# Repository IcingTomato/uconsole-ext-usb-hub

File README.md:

Licence | OSHWA
:-------------------------:|:-------------------------:
 | 

# uConsole USB Hub

This extension board adds 4 additional USB ports to the [uConsole](https://www.clockworkpi.com/uconsole).

## Schematic

## PCB

## Changelog
* 0.1.1
    * Schematic
        * No changes
    * PCB
        * Add OSHW certification
        * Add some info labels and QR code to this repo
* 0.1.0 -- **Production Release**
    * Schematic
        * `HUB_RESET` is now connected to `GPIO28`
        * `U3`, `U4`, `U5`, `U6` are rotated to simplify pcb
    * PCB
        * First PCB version
* 0.0.2
    * Schematic
        * Add speakers
* 0.0.1
    * Initial release

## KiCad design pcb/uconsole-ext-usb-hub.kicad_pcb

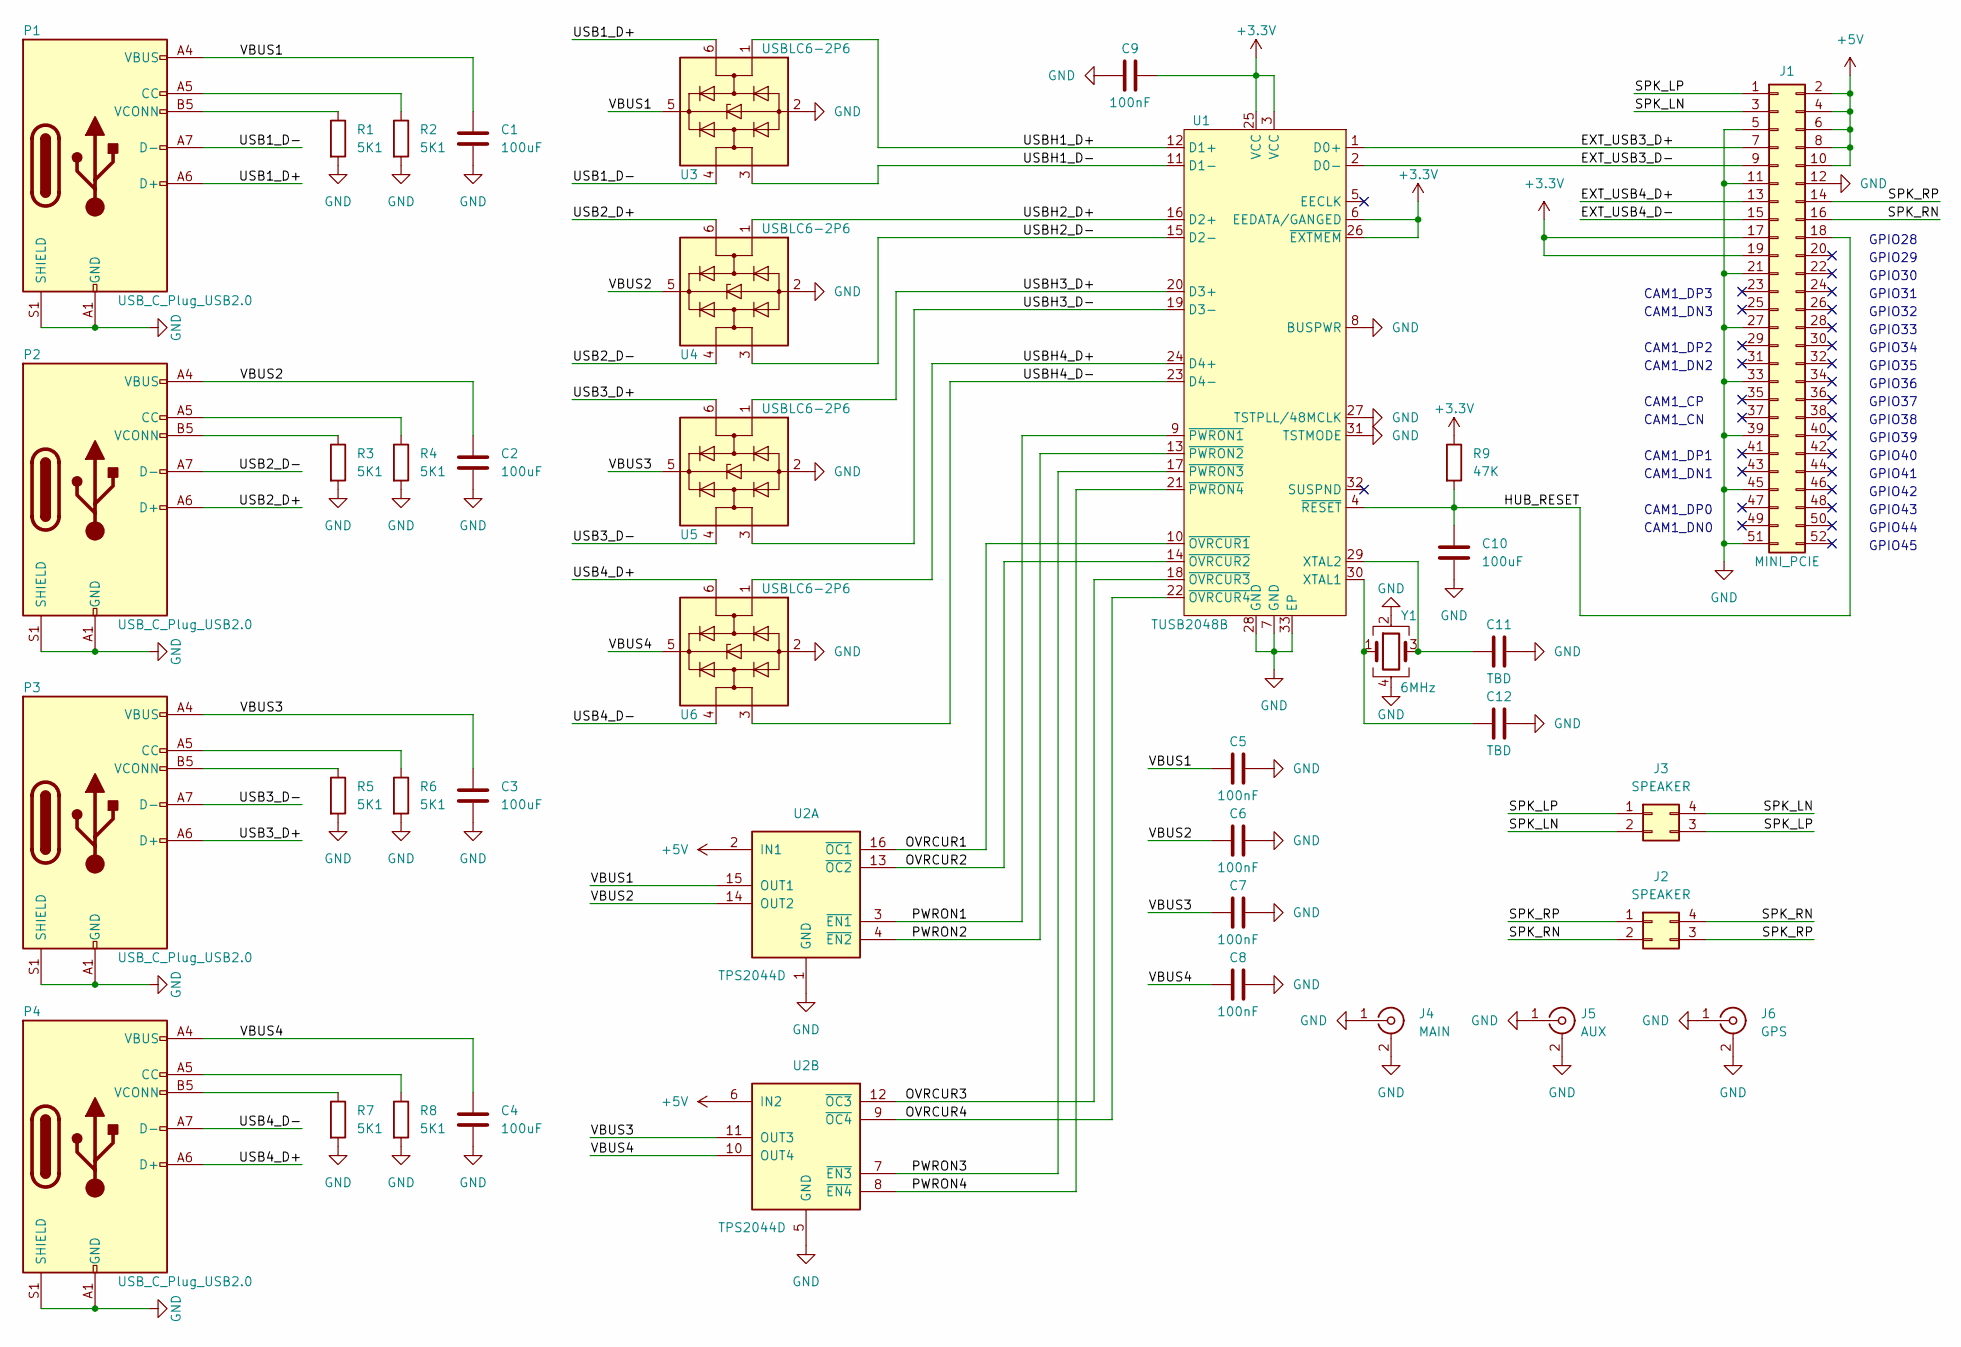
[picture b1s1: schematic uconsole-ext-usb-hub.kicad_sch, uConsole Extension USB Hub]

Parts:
C1, C2, C3, C4, C10: 100uF; C_0805_2012Metric
C5, C6, C7, C8, C9: 100nF; C_0603_1608Metric
C11, C12: TBD; C_0603_1608Metric
J1: MINI_PCIE; mini_pcie_edge
J2, J3: SPEAKER; uConsole_speaker
J4: MAIN; U.FL_Hirose_U.FL-R-SMT-1_Vertical
J5: AUX; U.FL_Hirose_U.FL-R-SMT-1_Vertical
J6: GPS; U.FL_Hirose_U.FL-R-SMT-1_Vertical
P1, P2, P3, P4: USB_C_Plug_USB2.0; USB_C_Receptacle_GCT_USB4105-xx-A_16P_TopMnt_Horizontal
R1, R2, R3, R4, R5, R6, R7, R8: 5K1; R_0603_1608Metric
R9: 47K; R_0603_1608Metric
U1: TUSB2048B; QFN-32-1EP_5x5mm_P0.5mm_EP3.3x3.3mm_ThermalVias
U2: TPS2044D; SOIC-16_3.9x9.9mm_P1.27mm
U3, U4, U5, U6: USBLC6-2P6; SOT-666
Y1: 6MHz; Crystal_SMD_2016-4Pin_2.0x1.6mm

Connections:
+3.3V: C9.1, J1.17, J1.19, R9.1, U1.3 (VCC), U1.6 (EEDATA/GANGED), U1.25 (VCC), U1.26 (~EXTMEM)
+5V: J1.2, J1.4, J1.6, J1.8, J1.10, U2.2 (IN1), U2.6 (IN2)
/EXT_USB3_D+: J1.7, U1.1 (D0+)
/EXT_USB3_D-: J1.9, U1.2 (D0-)
/EXT_USB4_D+: J1.13
/EXT_USB4_D-: J1.15
/HUB_RESET: C10.1, J1.18, R9.2, U1.4 (~RESET)
/OVRCUR1: U1.10 (~OVRCUR1), U2.16 (~OC1)
/OVRCUR2: U1.14 (~OVRCUR2), U2.13 (~OC2)
/OVRCUR3: U1.18 (~OVRCUR3), U2.12 (~OC3)
/OVRCUR4: U1.22 (~OVRCUR4), U2.9 (~OC4)
/PWRON1: U1.9 (~PWRON1), U2.3 (~EN1)
/PWRON2: U1.13 (~PWRON2), U2.4 (~EN2)
/PWRON3: U1.17 (~PWRON3), U2.7 (~EN3)
/PWRON4: U1.21 (~PWRON4), U2.8 (~EN4)
/SPK_LN: J1.3, J3.2, J3.4
/SPK_LP: J1.1, J3.1, J3.3
/SPK_RN: J1.16, J2.2, J2.4
/SPK_RP: J1.14, J2.1, J2.3
/USB1_D+: P1.A6 (D+), U3.6 (I/O1)
/USB1_D-: P1.A7 (D-), U3.4 (I/O2)
/USB2_D+: P2.A6 (D+), U4.6 (I/O1)
/USB2_D-: P2.A7 (D-), U4.4 (I/O2)
/USB3_D+: P3.A6 (D+), U5.6 (I/O1)
/USB3_D-: P3.A7 (D-), U5.4 (I/O2)
/USB4_D+: P4.A6 (D+), U6.6 (I/O1)
/USB4_D-: P4.A7 (D-), U6.4 (I/O2)
/USBH1_D+: U1.12 (D1+), U3.1 (I/O1)
/USBH1_D-: U1.11 (D1-), U3.3 (I/O2)
/USBH2_D+: U1.16 (D2+), U4.1 (I/O1)
/USBH2_D-: U1.15 (D2-), U4.3 (I/O2)
/USBH3_D+: U1.20 (D3+), U5.1 (I/O1)
/USBH3_D-: U1.19 (D3-), U5.3 (I/O2)
/USBH4_D+: U1.24 (D4+), U6.1 (I/O1)
/USBH4_D-: U1.23 (D4-), U6.3 (I/O2)
/VBUS1: C1.1, C5.1, P1.A4 (VBUS), P1.A9 (VBUS), P1.B4 (VBUS), P1.B9 (VBUS), U2.15 (OUT1), U3.5 (VBUS)
/VBUS2: C2.1, C6.1, P2.A4 (VBUS), P2.A9 (VBUS), P2.B4 (VBUS), P2.B9 (VBUS), U2.14 (OUT2), U4.5 (VBUS)
/VBUS3: C3.1, C7.1, P3.A4 (VBUS), P3.A9 (VBUS), P3.B4 (VBUS), P3.B9 (VBUS), U2.11 (OUT3), U5.5 (VBUS)
/VBUS4: C4.1, C8.1, P4.A4 (VBUS), P4.A9 (VBUS), P4.B4 (VBUS), P4.B9 (VBUS), U2.10 (OUT4), U6.5 (VBUS)
GND: C1.2, C2.2, C3.2, C4.2, C5.2, C6.2, C7.2, C8.2, C9.2, C10.2, C11.2, C12.2, J1.5, J1.11, J1.12, J1.21, J1.27, J1.33, J1.39, J1.45, J1.51, J4.1 (In), J4.2 (Ext), J5.1 (In), J5.2 (Ext), J6.1 (In), J6.2 (Ext), P1.A1 (GND), P1.A12 (GND), P1.B1 (GND), P1.B12 (GND), P1.S1 (SHIELD), P2.A1 (GND), P2.A12 (GND), P2.B1 (GND), P2.B12 (GND), P2.S1 (SHIELD), P3.A1 (GND), P3.A12 (GND), P3.B1 (GND), P3.B12 (GND), P3.S1 (SHIELD), P4.A1 (GND), P4.A12 (GND), P4.B1 (GND), P4.B12 (GND), P4.S1 (SHIELD), R1.2, R2.2, R3.2, R4.2, R5.2, R6.2, R7.2, R8.2, U1.7 (GND), U1.8 (BUSPWR), U1.27 (TSTPLL/48MCLK), U1.28 (GND), U1.31 (TSTMODE), U1.33 (EP), U2.1 (GND), U2.5 (GND), U3.2 (GND), U4.2 (GND), U5.2 (GND), U6.2 (GND), Y1.2, Y1.4
unnamed: P1.A5 (CC), R2.1
unnamed: P1.B5 (VCONN), R1.1
unnamed: P2.A5 (CC), R4.1
unnamed: P2.B5 (VCONN), R3.1
unnamed: P3.A5 (CC), R6.1
unnamed: P3.B5 (VCONN), R5.1
unnamed: P4.A5 (CC), R8.1
unnamed: P4.B5 (VCONN), R7.1
unnamed: C12.1, U1.30 (XTAL1), Y1.1
unnamed: C11.1, U1.29 (XTAL2), Y1.3

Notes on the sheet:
CAM1_DN1
GPIO43
CAM1_DP3
CAM1_DP0
GPIO31
GPIO42
CAM1_DN3
GPIO29
CAM1_DP2
GPIO41
CAM1_DP1
GPIO32
GPIO28
GPIO38
GPIO30
CAM1_DN2
CAM1_DN0
GPIO39
CAM1_CP
GPIO34
GPIO37
GPIO33
CAM1_CN
GPIO36
GPIO35
GPIO44
GPIO45
GPIO40

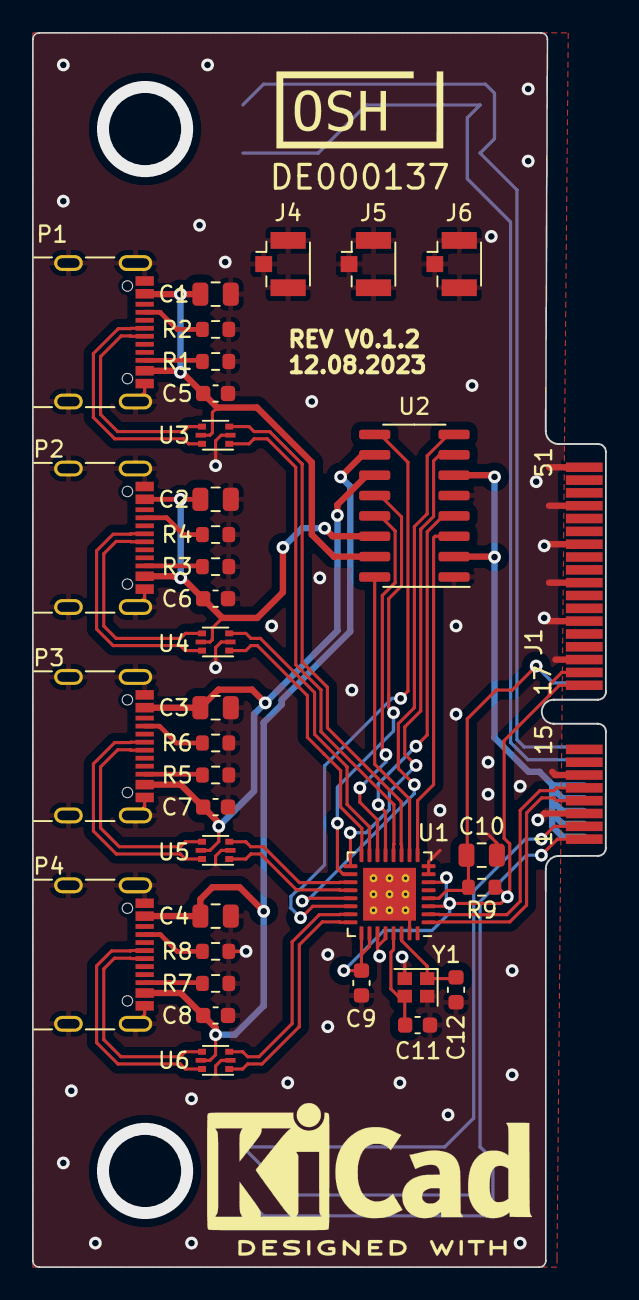
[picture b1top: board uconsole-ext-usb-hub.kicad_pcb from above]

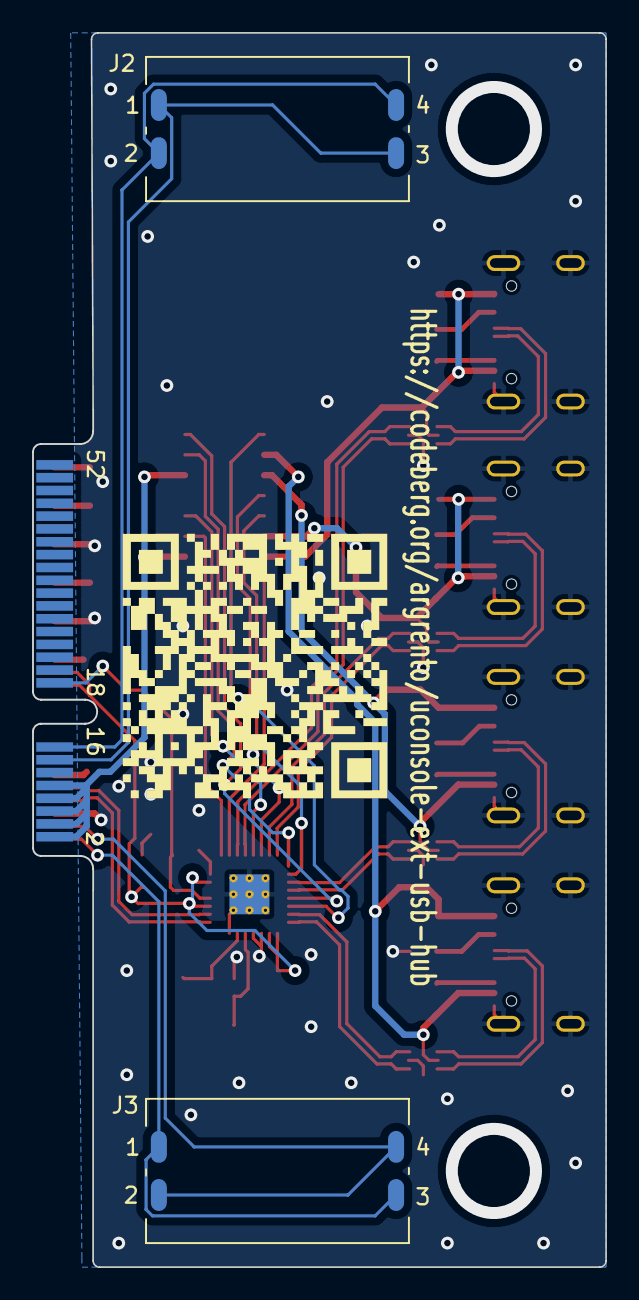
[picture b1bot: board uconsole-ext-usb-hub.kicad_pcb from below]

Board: 2 copper layers, 35.7 x 77.0 mm, 40 parts (3 on the bottom side), 48 nets.

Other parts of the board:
OSHW_Dual_0.25_Scale: DE000137; OSHW_Dual_0.25_Scale
QR: qr-https--codeberg.org-argrento-uconsole-ext-usb-hub

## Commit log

2023-08-12 Some updates of sch, pcb and readme
    * Add 3 u.fl connectors for antennas
    * Update pictures in readme
2023-08-13 ci: externalize project name
    * Project name is now in env variable for convenience
    * Number of layers is in in env vars
    * Inner layers are created if there are 4 layers only
    * Add csv BOM generation (Close #2)
    * Add InteractiveHtmlBom
    * Add OSHW logo (Close #3)
